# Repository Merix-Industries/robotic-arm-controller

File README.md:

# Simple Robotic Arm Controller

This project represents our initial foray into PCB design. It features a compact control board equipped with two potentiometers and a tactile button, specifically engineered to interface with a custom-built robotic arm.

---

## Features
* **Dual Potentiometers:** Enables high-precision servo control for smooth movement.
* **Dedicated Button:** Integrated trigger for seamless gripper operation.
* **ATmega328P Microcontroller:** Utilizes the robust AVR architecture for reliable processing.
* **Custom PCB Design:** Professionally routed and developed using **KiCad**.

---

## Technical Details

The core of the system is the **ATmega328P** microcontroller, programmed via the **Arduino IDE**. The firmware translates analog signals from the potentiometers into precise PWM outputs to govern the arm's rotation and reach, while the digital input from the button toggles the gripper mechanism.

### Hardware Configuration
| Component | Primary Function |
| :--- | :--- |
| **Potentiometer 1** | Reach Control |
| **Potentiometer 2** | Extension Control |
| **Tactile Button** | Gripper Actuation (Open/Close) |
| **Microcontroller** | ATmega328P (Standalone configuration) |

---

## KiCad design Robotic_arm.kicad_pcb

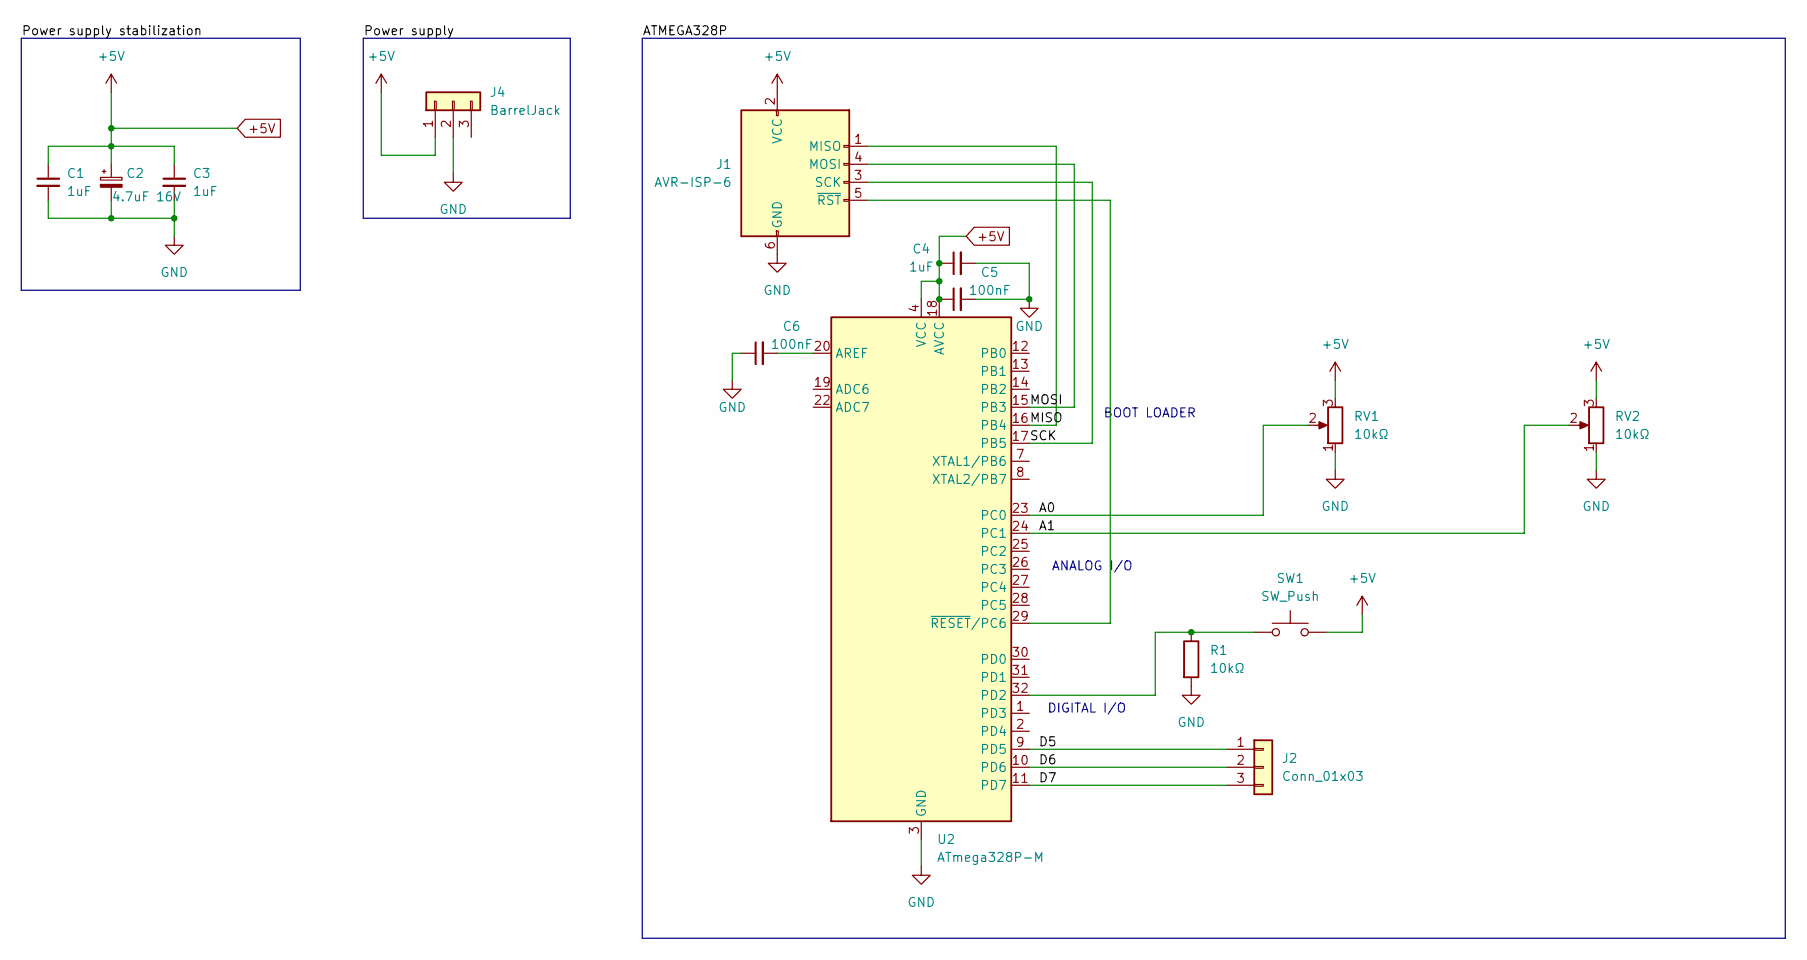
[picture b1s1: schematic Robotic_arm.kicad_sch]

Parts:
C1, C3, C4: 1uF; C_0201_0603Metric
C2: 4.7uF 16V; C_0201_0603Metric
C5, C6: 100nF; C_0201_0603Metric
J1: AVR-ISP-6; Harwin_LTek-Male_2x03_P2.00mm_Vertical_StrainRelief
J2: Conn_01x03; PinHeader_1x03_P2.54mm_Vertical
J4: BarrelJack; BarrelJack_CUI_PJ-102AH_Horizontal
R1: 10kΩ; R_0201_0603Metric
RV1, RV2: 10kΩ; Potentiometer_ACP_CA9-V10_Vertical
SW1: SW_Push; SW_TH_Tactile_Omron_B3F-10xx
U2: ATmega328P-M; QFN-32-1EP_5x5mm_P0.5mm_EP3.1x3.1mm

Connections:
+5V: C1.1, C2.1, C3.1, C4.1, C5.1, J1.2 (VCC), J4.1, RV1.3, RV2.3, SW1.2, U2.4 (VCC), U2.6 (VCC), U2.18 (AVCC)
/A0: RV1.2, U2.23 (PC0)
/A1: RV2.2, U2.24 (PC1)
/D5: J2.1, U2.9 (PD5)
/D6: J2.2, U2.10 (PD6)
/D7: J2.3, U2.11 (PD7)
/MISO: J1.1 (MISO), U2.16 (PB4)
/MOSI: J1.4 (MOSI), U2.15 (PB3)
/SCK: J1.3 (SCK), U2.17 (PB5)
GND: C1.2, C2.2, C3.2, C4.2, C5.2, C6.1, J1.6 (GND), J4.2, R1.2, RV1.1, RV2.1, U2.3 (GND), U2.5 (GND), U2.21 (GND), U2.33 (GND)
unnamed: J1.5 (~RST), U2.29 (~RESET/PC6)
unnamed: C6.2, U2.20 (AREF)
unnamed: R1.1, SW1.1, U2.32 (PD2)

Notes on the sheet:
BOOT LOADER
ANALOG I/O
DIGITAL I/O

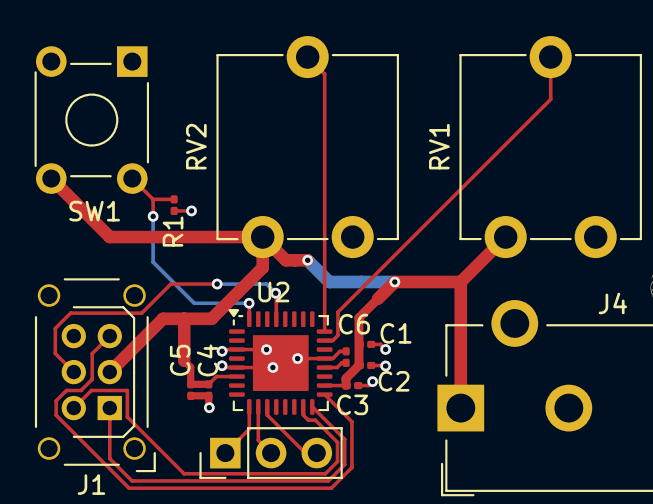
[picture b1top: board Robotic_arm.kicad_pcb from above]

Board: 2 copper layers, 14 parts (0 on the bottom side), 13 nets.

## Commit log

2026-01-30 Revise README for improved clarity and structure
    Updated README to enhance formatting and add features.
2026-02-06 Upload of all the files for this project
